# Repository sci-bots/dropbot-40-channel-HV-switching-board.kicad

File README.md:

# DropBot v3 40-channel high-voltage switching board

The high-voltage switching boards control the on/off state of electrodes in the [DropBot system][dropbot]. Each board controls 40-channels and multiple boards can be daisy-chained together.

For more information, please visit https://sci-bots.com

[][sci-bots]

This design is open-source hardware released under a [Creative Commons Attribution-ShareAlike licence][cc-by-sa].

[][cc-by-sa]

[dropbot]: https://github.com/sci-bots/dropbot-v3
[sci-bots]: https://sci-bots.com/
[cc-by-sa]: http://creativecommons.org/licenses/by-sa/3.0

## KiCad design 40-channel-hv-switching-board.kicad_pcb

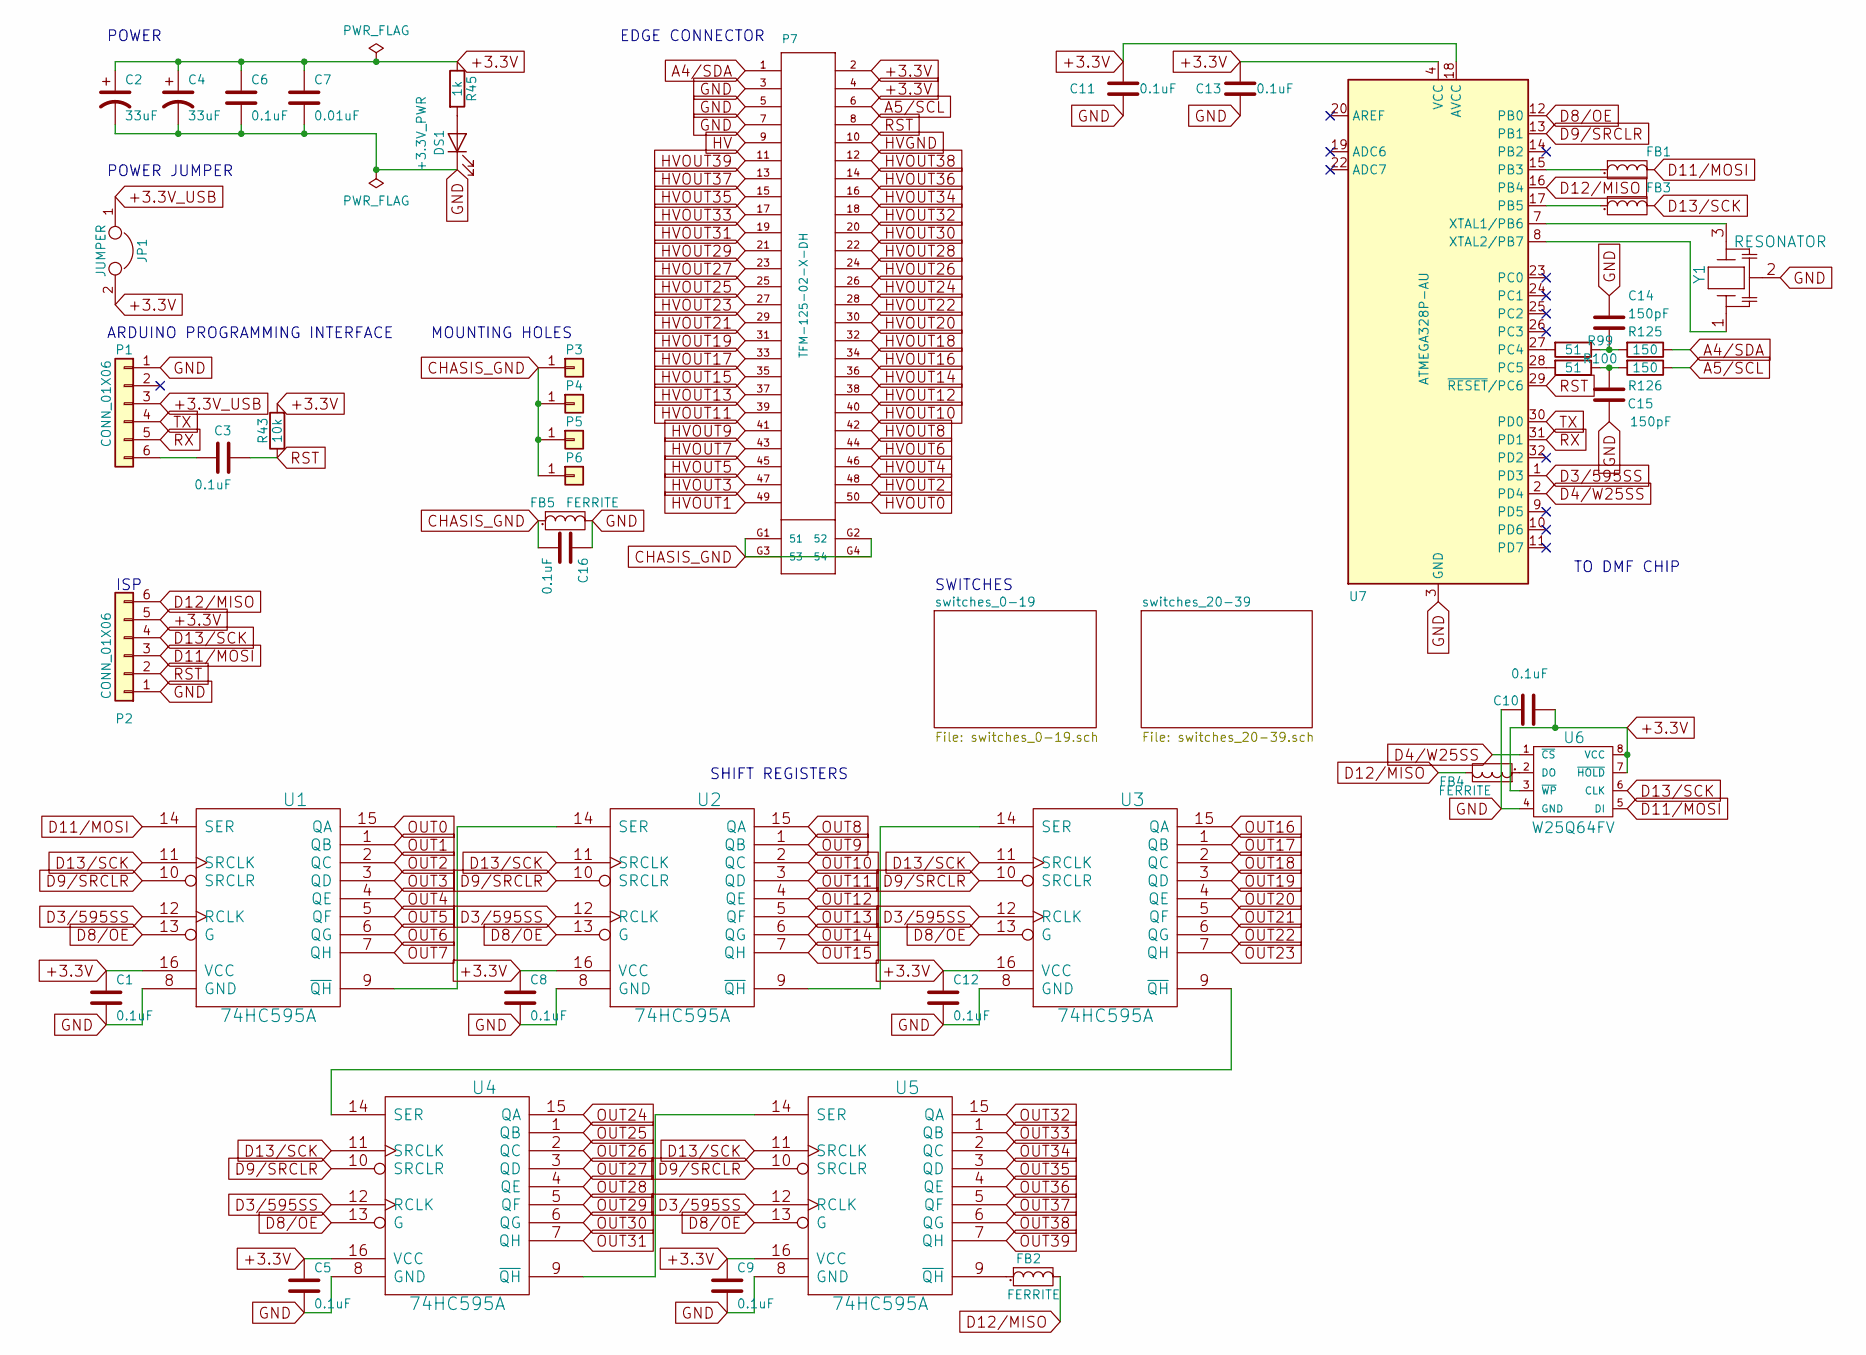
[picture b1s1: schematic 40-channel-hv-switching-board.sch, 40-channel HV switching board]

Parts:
C1, C3, C5, C6, C8, C9, C10, C11, C12, C13, C16: 0.1uF; C_0805; MPN CL21B104KBCNNNC
C2, C4: 33uF; SM2917; MPN T491D336K020AT
C7: 0.01uF; C_0805; MPN CL21B103KCANNNC
C14, C15: 150pF; C_0805; MPN CL21C151JBANNNC
DS1: +3.3V_PWR; LED_0805; MPN 150080BS75000
FB1, FB2, FB3, FB4, FB5: FERRITE; R_0805; MPN 742792040
JP1: JUMPER; R_0805; MPN DNP
P1: CONN_01X06; Pin_Header_Angled_1x06; MPN DNP
P2: CONN_01X06; Pin_Header_Straight_2x03; MPN DNP
P3, P4, P5, P6: CONN_01X01; 1pin; MPN DNP
P7: TFM-125-02-X-DH; MPN TFM-125-02-L-DH
R43: 10k; R_0805; MPN RC0805FR-0710KL
R45: 1k; R_0805; MPN RC0805FR-071KL
R99, R100: 51; R_0805; MPN RC0805FR-0751RL
R125, R126: 150; R_0805; MPN RC0805FR-07150RL
U1, U2, U3, U4, U5: 74HC595A; SO16E; MPN MM74HC595MX
U6: W25Q64FV; SOIC-8-N; MPN W25Q64FVSSIG TR
U7: ATMEGA328P-AU; TQFP-32_7x7mm_Pitch0.8mm; MPN ATMEGA328P-AU
Y1: RESONATOR; CSTCE_G15C; MPN CSTCE8M00G55-R0

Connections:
+3.3V: C1.1, C2.1, C4.1, C5.1, C6.1, C7.1, C8.1, C9.1, C10.1, C11.2, C12.1, C13.2, JP1.2, P2.5, P7.2, P7.4, R43.2, R45.1, U1.16 (VCC), U2.16 (VCC), U3.16 (VCC), U4.16 (VCC), U5.16 (VCC), U6.3 (~WP), U6.7 (~HOLD), U6.8 (VCC), U7.4 (VCC), U7.6 (VCC), U7.18 (AVCC); also elsewhere on the board
+3.3V_USB: JP1.1, P1.3
A4/SDA: P7.1, R125.1
A5/SCL: P7.6, R126.1
CHASIS_GND: C16.2, FB5.1, P3.1, P4.1, P5.1, P6.1, P7.G1 (51), P7.G2 (52), P7.G3 (53), P7.G4 (54)
D3/595SS: U1.12 (RCLK), U2.12 (RCLK), U3.12 (RCLK), U4.12 (RCLK), U5.12 (RCLK), U7.1 (PD3)
D4/W25SS: U6.1 (~CS), U7.2 (PD4)
D8/OE: U1.13 (G), U2.13 (G), U3.13 (G), U4.13 (G), U5.13 (G), U7.12 (PB0)
D9/SRCLR: U1.10 (SRCLR), U2.10 (SRCLR), U3.10 (SRCLR), U4.10 (SRCLR), U5.10 (SRCLR), U7.13 (PB1)
D11/MOSI: FB1.2, P2.3, U1.14 (SER), U6.5 (DI)
D12/MISO: FB2.2, FB4.2, P2.6, U7.16 (PB4)
D13/SCK: FB3.2, P2.4, U1.11 (SRCLK), U2.11 (SRCLK), U3.11 (SRCLK), U4.11 (SRCLK), U5.11 (SRCLK), U6.6 (CLK)
GND: C1.2, C2.2, C4.2, C5.2, C6.2, C7.2, C8.2, C9.2, C10.2, C11.1, C12.2, C13.1, C14.1, C15.1, C16.1, DS1.1 (K), FB5.2, P1.1, P2.1, P7.3, P7.5, P7.7, U1.8 (GND), U2.8 (GND), U3.8 (GND), U4.8 (GND), U5.8 (GND), U6.4 (GND), U7.3 (GND), U7.5 (GND), U7.21 (GND), Y1.2; also elsewhere on the board
HV: P7.9; also elsewhere on the board
HVGND: P7.10; also elsewhere on the board
HVOUT0: P7.50; also elsewhere on the board
HVOUT1: P7.49; also elsewhere on the board
HVOUT2: P7.48; also elsewhere on the board
HVOUT3: P7.47; also elsewhere on the board
HVOUT4: P7.46; also elsewhere on the board
HVOUT5: P7.45; also elsewhere on the board
HVOUT6: P7.44; also elsewhere on the board
HVOUT7: P7.43; also elsewhere on the board
HVOUT8: P7.42; also elsewhere on the board
HVOUT9: P7.41; also elsewhere on the board
HVOUT10: P7.40; also elsewhere on the board
HVOUT11: P7.39; also elsewhere on the board
HVOUT12: P7.38; also elsewhere on the board
HVOUT13: P7.37; also elsewhere on the board
HVOUT14: P7.36; also elsewhere on the board
HVOUT15: P7.35; also elsewhere on the board
HVOUT16: P7.34; also elsewhere on the board
HVOUT17: P7.33; also elsewhere on the board
HVOUT18: P7.32; also elsewhere on the board
HVOUT19: P7.31; also elsewhere on the board
HVOUT20: P7.30; also elsewhere on the board
HVOUT21: P7.29; also elsewhere on the board
HVOUT22: P7.28; also elsewhere on the board
HVOUT23: P7.27; also elsewhere on the board
HVOUT24: P7.26; also elsewhere on the board
HVOUT25: P7.25; also elsewhere on the board
HVOUT26: P7.24; also elsewhere on the board
HVOUT27: P7.23; also elsewhere on the board
HVOUT28: P7.22; also elsewhere on the board
HVOUT29: P7.21; also elsewhere on the board
HVOUT30: P7.20; also elsewhere on the board
HVOUT31: P7.19; also elsewhere on the board
HVOUT32: P7.18; also elsewhere on the board
HVOUT33: P7.17; also elsewhere on the board
HVOUT34: P7.16; also elsewhere on the board
HVOUT35: P7.15; also elsewhere on the board
HVOUT36: P7.14; also elsewhere on the board
HVOUT37: P7.13; also elsewhere on the board
HVOUT38: P7.12; also elsewhere on the board
HVOUT39: P7.11; also elsewhere on the board
unnamed: C3.1, P1.6
unnamed: C14.2, R99.1, R125.2
unnamed: C15.2, R100.1, R126.2
unnamed: DS1.2 (A), R45.2
unnamed: FB1.1, U7.15 (PB3)
unnamed: FB2.1, U5.9 (~QH)
unnamed: FB3.1, U7.17 (PB5)
unnamed: FB4.1, U6.2 (DO)
unnamed: R99.2, U7.27 (PC4)
unnamed: R100.2, U7.28 (PC5)
unnamed: U1.9 (~QH), U2.14 (SER)
unnamed: U2.9 (~QH), U3.14 (SER)
unnamed: U3.9 (~QH), U4.14 (SER)
unnamed: U4.9 (~QH), U5.14 (SER)
unnamed: U7.7 (XTAL1/PB6), Y1.3
unnamed: U7.8 (XTAL2/PB7), Y1.1
OUT0: U1.15 (QA); also elsewhere on the board
OUT1: U1.1 (QB); also elsewhere on the board
OUT2: U1.2 (QC); also elsewhere on the board
OUT3: U1.3 (QD); also elsewhere on the board
OUT4: U1.4 (QE); also elsewhere on the board
OUT5: U1.5 (QF); also elsewhere on the board
OUT6: U1.6 (QG); also elsewhere on the board
OUT7: U1.7 (QH); also elsewhere on the board
OUT8: U2.15 (QA); also elsewhere on the board
OUT9: U2.1 (QB); also elsewhere on the board
OUT10: U2.2 (QC); also elsewhere on the board
OUT11: U2.3 (QD); also elsewhere on the board
OUT12: U2.4 (QE); also elsewhere on the board
OUT13: U2.5 (QF); also elsewhere on the board
OUT14: U2.6 (QG); also elsewhere on the board
OUT15: U2.7 (QH); also elsewhere on the board
OUT16: U3.15 (QA); also elsewhere on the board
OUT17: U3.1 (QB); also elsewhere on the board
OUT18: U3.2 (QC); also elsewhere on the board
OUT19: U3.3 (QD); also elsewhere on the board
OUT20: U3.4 (QE); also elsewhere on the board
OUT21: U3.5 (QF); also elsewhere on the board
OUT22: U3.6 (QG); also elsewhere on the board
OUT23: U3.7 (QH); also elsewhere on the board
OUT24: U4.15 (QA); also elsewhere on the board
OUT25: U4.1 (QB); also elsewhere on the board
OUT26: U4.2 (QC); also elsewhere on the board
OUT27: U4.3 (QD); also elsewhere on the board
OUT28: U4.4 (QE); also elsewhere on the board
OUT29: U4.5 (QF); also elsewhere on the board
OUT30: U4.6 (QG); also elsewhere on the board
OUT31: U4.7 (QH); also elsewhere on the board
OUT32: U5.15 (QA); also elsewhere on the board
OUT33: U5.1 (QB); also elsewhere on the board
OUT34: U5.2 (QC); also elsewhere on the board
OUT35: U5.3 (QD); also elsewhere on the board
OUT36: U5.4 (QE); also elsewhere on the board
OUT37: U5.5 (QF); also elsewhere on the board
OUT38: U5.6 (QG); also elsewhere on the board
OUT39: U5.7 (QH); also elsewhere on the board
RST: C3.2, P2.2, P7.8, R43.1, U7.29 (~RESET~/PC6)
RX: P1.5, U7.31 (PD1)
TX: P1.4, U7.30 (PD0)

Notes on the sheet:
SHIFT REGISTERS
TO DMF CHIP
POWER
ARDUINO PROGRAMMING INTERFACE
ISP
POWER JUMPER
SWITCHES
EDGE CONNECTOR
MOUNTING HOLES

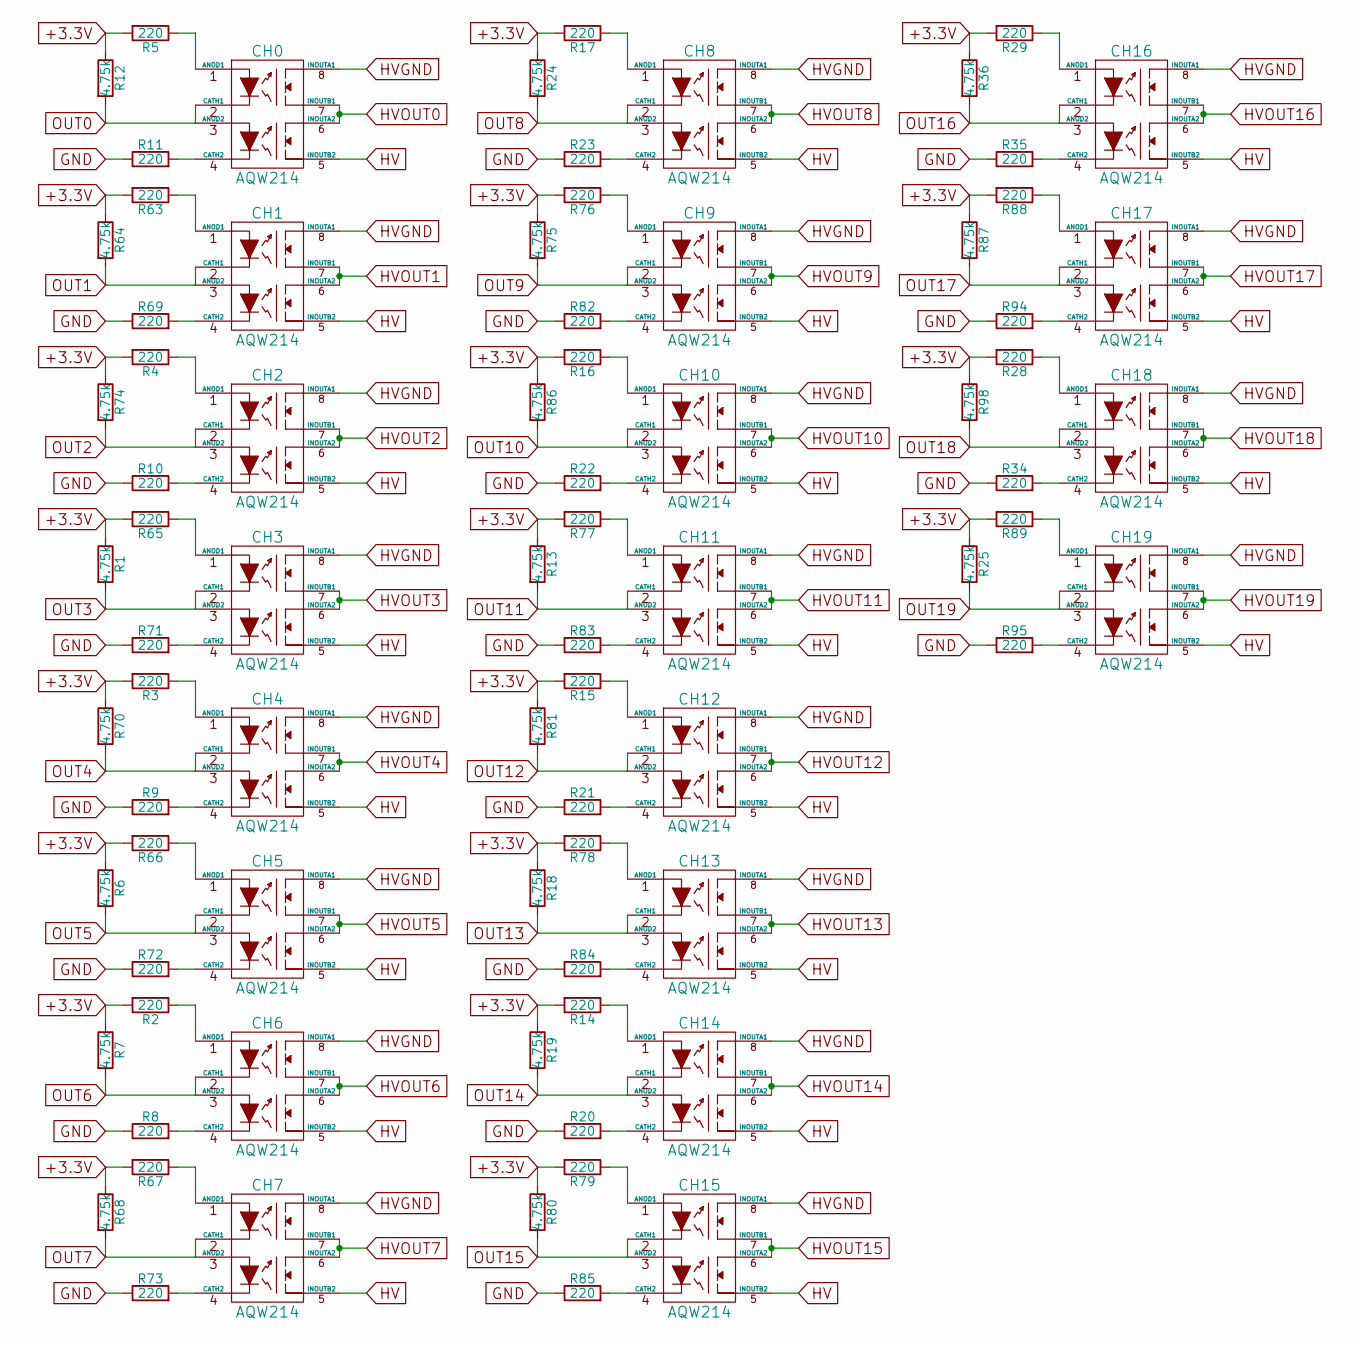
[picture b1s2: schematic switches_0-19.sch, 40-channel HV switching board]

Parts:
CH0, CH1, CH2, CH3, CH4, CH5, CH6, CH7, CH8, CH9, CH10, CH11, CH12, CH13, CH14, CH15, CH16, CH17, CH18, CH19: AQW214; DIP-8_SMD; Mfg_Part_No TLP227G-2(TP1,N,F)
R1, R6, R7, R12, R13, R18, R19, R25, R36, R64, R68, R70, R74, R75, R80, R81, R86, R87, R98: 4.75k; R_0805
R2, R3, R4, R5, R8, R9, R10, R11, R14, R15, R16, R17, R20, R21, R22, R23, R28, R29, R34, R35, R63, R65, R66, R69, R71, R72, R73, R76, R77, R78, R79, R82, R83, R84, R85, R88, R89, R94, R95: 220; R_0805
R24: 4.75k; R_0805; Mfg_Part_No RC0805FR-074K75L
R67: 220; R_0805; Mfg_Part_No RC0805FR-07220RL

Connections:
+3.3V: R1.1, R2.2, R3.2, R4.2, R5.2, R6.1, R7.1, R12.1, R13.1, R14.2, R15.2, R16.2, R17.2, R18.1, R19.1, R24.1, R25.1, R28.2, R29.2, R36.1, R63.2, R64.1, R65.2, R66.2, R67.2, R68.1, R70.1, R74.1, R75.1, R76.2, R77.2, R78.2, R79.2, R80.1, R81.1, R86.1, R87.1, R88.2, R89.2, R98.1; also elsewhere on the board
GND: R8.1, R9.1, R10.1, R11.1, R20.1, R21.1, R22.1, R23.1, R34.1, R35.1, R69.1, R71.1, R72.1, R73.1, R82.1, R83.1, R84.1, R85.1, R94.1, R95.1; also elsewhere on the board
HV: CH0.5 (INOUTB2), CH1.5 (INOUTB2), CH2.5 (INOUTB2), CH3.5 (INOUTB2), CH4.5 (INOUTB2), CH5.5 (INOUTB2), CH6.5 (INOUTB2), CH7.5 (INOUTB2), CH8.5 (INOUTB2), CH9.5 (INOUTB2), CH10.5 (INOUTB2), CH11.5 (INOUTB2), CH12.5 (INOUTB2), CH13.5 (INOUTB2), CH14.5 (INOUTB2), CH15.5 (INOUTB2), CH16.5 (INOUTB2), CH17.5 (INOUTB2), CH18.5 (INOUTB2), CH19.5 (INOUTB2); also elsewhere on the board
HVGND: CH0.8 (INOUTA1), CH1.8 (INOUTA1), CH2.8 (INOUTA1), CH3.8 (INOUTA1), CH4.8 (INOUTA1), CH5.8 (INOUTA1), CH6.8 (INOUTA1), CH7.8 (INOUTA1), CH8.8 (INOUTA1), CH9.8 (INOUTA1), CH10.8 (INOUTA1), CH11.8 (INOUTA1), CH12.8 (INOUTA1), CH13.8 (INOUTA1), CH14.8 (INOUTA1), CH15.8 (INOUTA1), CH16.8 (INOUTA1), CH17.8 (INOUTA1), CH18.8 (INOUTA1), CH19.8 (INOUTA1); also elsewhere on the board
HVOUT0: CH0.6 (INOUTA2), CH0.7 (INOUTB1); also elsewhere on the board
HVOUT1: CH1.6 (INOUTA2), CH1.7 (INOUTB1); also elsewhere on the board
HVOUT2: CH2.6 (INOUTA2), CH2.7 (INOUTB1); also elsewhere on the board
HVOUT3: CH3.6 (INOUTA2), CH3.7 (INOUTB1); also elsewhere on the board
HVOUT4: CH4.6 (INOUTA2), CH4.7 (INOUTB1); also elsewhere on the board
HVOUT5: CH5.6 (INOUTA2), CH5.7 (INOUTB1); also elsewhere on the board
HVOUT6: CH6.6 (INOUTA2), CH6.7 (INOUTB1); also elsewhere on the board
HVOUT7: CH7.6 (INOUTA2), CH7.7 (INOUTB1); also elsewhere on the board
HVOUT8: CH8.6 (INOUTA2), CH8.7 (INOUTB1); also elsewhere on the board
HVOUT9: CH9.6 (INOUTA2), CH9.7 (INOUTB1); also elsewhere on the board
HVOUT10: CH10.6 (INOUTA2), CH10.7 (INOUTB1); also elsewhere on the board
HVOUT11: CH11.6 (INOUTA2), CH11.7 (INOUTB1); also elsewhere on the board
HVOUT12: CH12.6 (INOUTA2), CH12.7 (INOUTB1); also elsewhere on the board
HVOUT13: CH13.6 (INOUTA2), CH13.7 (INOUTB1); also elsewhere on the board
HVOUT14: CH14.6 (INOUTA2), CH14.7 (INOUTB1); also elsewhere on the board
HVOUT15: CH15.6 (INOUTA2), CH15.7 (INOUTB1); also elsewhere on the board
HVOUT16: CH16.6 (INOUTA2), CH16.7 (INOUTB1); also elsewhere on the board
HVOUT17: CH17.6 (INOUTA2), CH17.7 (INOUTB1); also elsewhere on the board
HVOUT18: CH18.6 (INOUTA2), CH18.7 (INOUTB1); also elsewhere on the board
HVOUT19: CH19.6 (INOUTA2), CH19.7 (INOUTB1); also elsewhere on the board
unnamed: CH0.1 (ANOD1), R5.1
unnamed: CH0.4 (CATH2), R11.2
unnamed: CH1.1 (ANOD1), R63.1
unnamed: CH1.4 (CATH2), R69.2
unnamed: CH2.1 (ANOD1), R4.1
unnamed: CH2.4 (CATH2), R10.2
unnamed: CH3.1 (ANOD1), R65.1
unnamed: CH3.4 (CATH2), R71.2
unnamed: CH4.1 (ANOD1), R3.1
unnamed: CH4.4 (CATH2), R9.2
unnamed: CH5.1 (ANOD1), R66.1
unnamed: CH5.4 (CATH2), R72.2
unnamed: CH6.1 (ANOD1), R2.1
unnamed: CH6.4 (CATH2), R8.2
unnamed: CH7.1 (ANOD1), R67.1
unnamed: CH7.4 (CATH2), R73.2
unnamed: CH8.1 (ANOD1), R17.1
unnamed: CH8.4 (CATH2), R23.2
unnamed: CH9.1 (ANOD1), R76.1
unnamed: CH9.4 (CATH2), R82.2
unnamed: CH10.1 (ANOD1), R16.1
unnamed: CH10.4 (CATH2), R22.2
unnamed: CH11.1 (ANOD1), R77.1
unnamed: CH11.4 (CATH2), R83.2
unnamed: CH12.1 (ANOD1), R15.1
unnamed: CH12.4 (CATH2), R21.2
unnamed: CH13.1 (ANOD1), R78.1
unnamed: CH13.4 (CATH2), R84.2
unnamed: CH14.1 (ANOD1), R14.1
unnamed: CH14.4 (CATH2), R20.2
unnamed: CH15.1 (ANOD1), R79.1
unnamed: CH15.4 (CATH2), R85.2
unnamed: CH16.1 (ANOD1), R29.1
unnamed: CH16.4 (CATH2), R35.2
unnamed: CH17.1 (ANOD1), R88.1
unnamed: CH17.4 (CATH2), R94.2
unnamed: CH18.1 (ANOD1), R28.1
unnamed: CH18.4 (CATH2), R34.2
unnamed: CH19.1 (ANOD1), R89.1
unnamed: CH19.4 (CATH2), R95.2
OUT0: CH0.2 (CATH1), CH0.3 (ANOD2), R12.2; also elsewhere on the board
OUT1: CH1.2 (CATH1), CH1.3 (ANOD2), R64.2; also elsewhere on the board
OUT2: CH2.2 (CATH1), CH2.3 (ANOD2), R74.2; also elsewhere on the board
OUT3: CH3.2 (CATH1), CH3.3 (ANOD2), R1.2; also elsewhere on the board
OUT4: CH4.2 (CATH1), CH4.3 (ANOD2), R70.2; also elsewhere on the board
OUT5: CH5.2 (CATH1), CH5.3 (ANOD2), R6.2; also elsewhere on the board
OUT6: CH6.2 (CATH1), CH6.3 (ANOD2), R7.2; also elsewhere on the board
OUT7: CH7.2 (CATH1), CH7.3 (ANOD2), R68.2; also elsewhere on the board
OUT8: CH8.2 (CATH1), CH8.3 (ANOD2), R24.2; also elsewhere on the board
OUT9: CH9.2 (CATH1), CH9.3 (ANOD2), R75.2; also elsewhere on the board
OUT10: CH10.2 (CATH1), CH10.3 (ANOD2), R86.2; also elsewhere on the board
OUT11: CH11.2 (CATH1), CH11.3 (ANOD2), R13.2; also elsewhere on the board
OUT12: CH12.2 (CATH1), CH12.3 (ANOD2), R81.2; also elsewhere on the board
OUT13: CH13.2 (CATH1), CH13.3 (ANOD2), R18.2; also elsewhere on the board
OUT14: CH14.2 (CATH1), CH14.3 (ANOD2), R19.2; also elsewhere on the board
OUT15: CH15.2 (CATH1), CH15.3 (ANOD2), R80.2; also elsewhere on the board
OUT16: CH16.2 (CATH1), CH16.3 (ANOD2), R36.2; also elsewhere on the board
OUT17: CH17.2 (CATH1), CH17.3 (ANOD2), R87.2; also elsewhere on the board
OUT18: CH18.2 (CATH1), CH18.3 (ANOD2), R98.2; also elsewhere on the board
OUT19: CH19.2 (CATH1), CH19.3 (ANOD2), R25.2; also elsewhere on the board

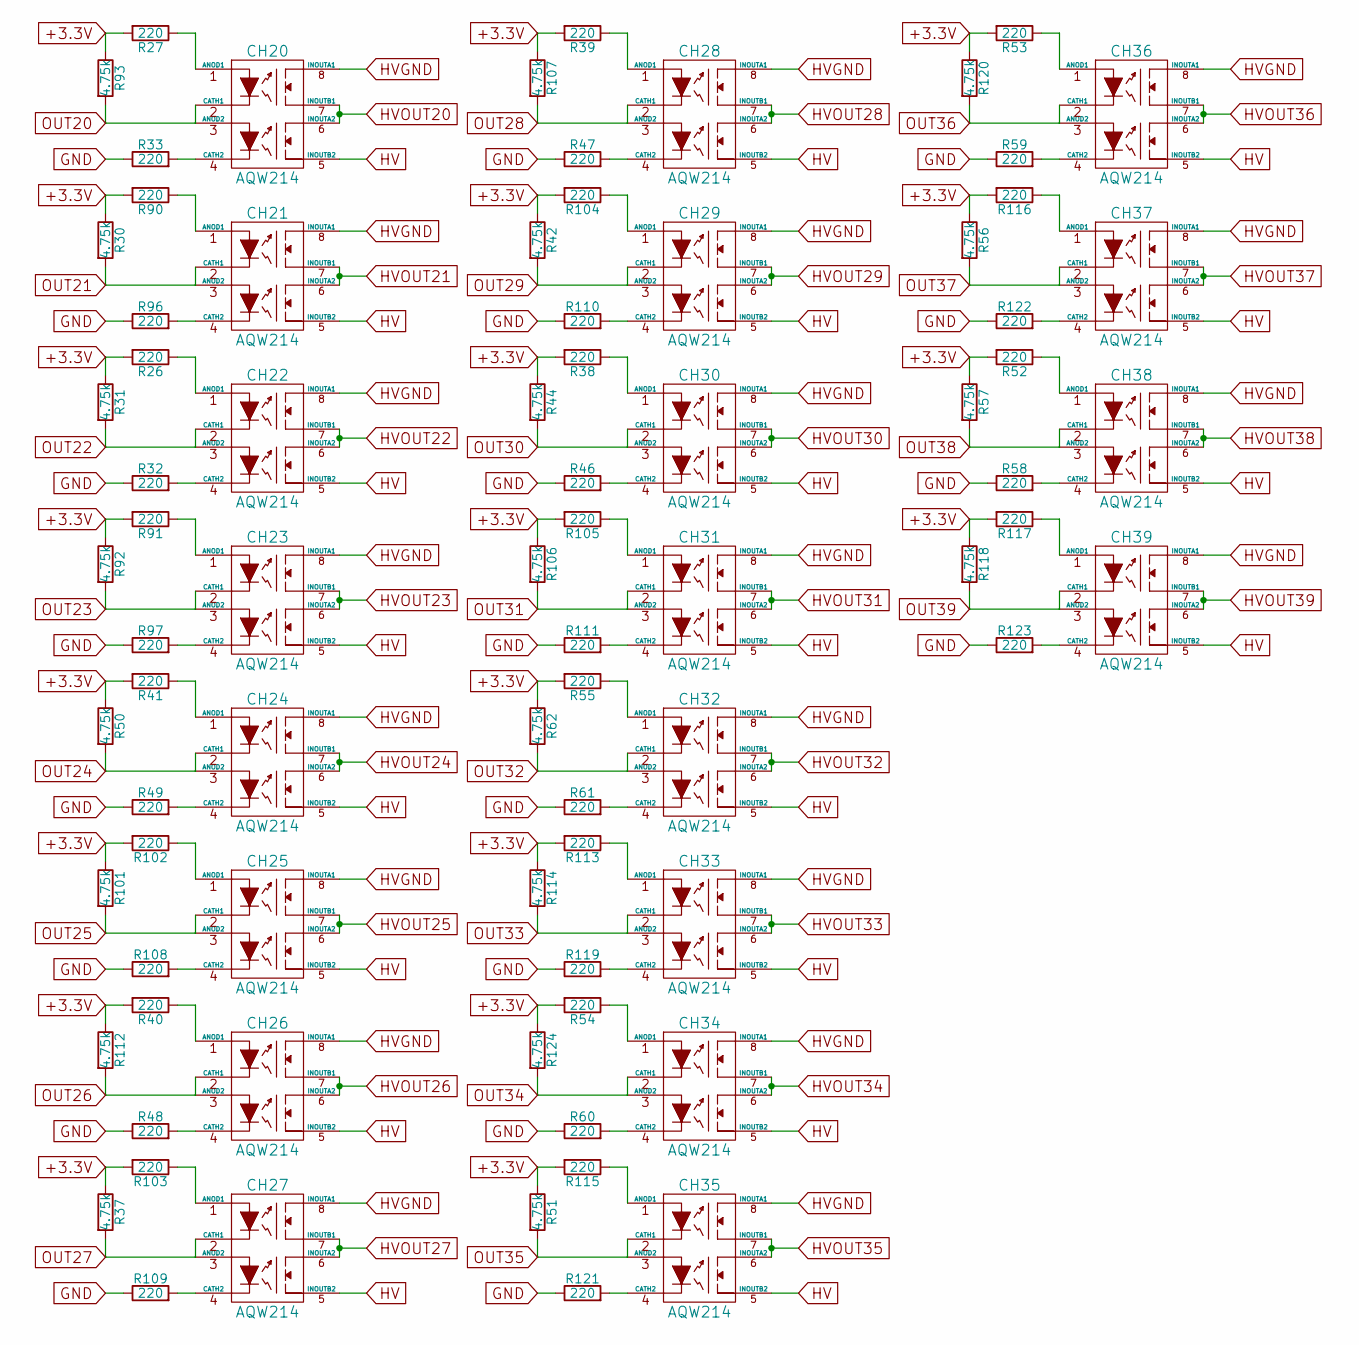
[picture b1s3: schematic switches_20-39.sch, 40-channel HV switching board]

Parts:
CH20, CH21, CH22, CH23, CH24, CH25, CH26, CH27, CH28, CH29, CH30, CH31, CH32, CH33, CH34, CH35, CH36, CH37, CH38, CH39: AQW214; DIP-8_SMD; Mfg_Part_No TLP227G-2(TP1,N,F)
R26, R27, R32, R33, R38, R39, R40, R41, R46, R47, R48, R49, R52, R53, R54, R55, R58, R59, R60, R61, R90, R91, R96, R97, R102, R103, R104, R105, R108, R109, R110, R111, R113, R115, R116, R117, R119, R121, R122, R123: 220; R_0805
R30, R31, R37, R42, R44, R50, R51, R56, R57, R62, R92, R93, R101, R106, R107, R112, R114, R118, R120, R124: 4.75k; R_0805

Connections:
+3.3V: R26.2, R27.2, R30.1, R31.1, R37.1, R38.2, R39.2, R40.2, R41.2, R42.1, R44.1, R50.1, R51.1, R52.2, R53.2, R54.2, R55.2, R56.1, R57.1, R62.1, R90.2, R91.2, R92.1, R93.1, R101.1, R102.2, R103.2, R104.2, R105.2, R106.1, R107.1, R112.1, R113.2, R114.1, R115.2, R116.2, R117.2, R118.1, R120.1, R124.1; also elsewhere on the board
GND: R32.1, R33.1, R46.1, R47.1, R48.1, R49.1, R58.1, R59.1, R60.1, R61.1, R96.1, R97.1, R108.1, R109.1, R110.1, R111.1, R119.1, R121.1, R122.1, R123.1; also elsewhere on the board
HV: CH20.5 (INOUTB2), CH21.5 (INOUTB2), CH22.5 (INOUTB2), CH23.5 (INOUTB2), CH24.5 (INOUTB2), CH25.5 (INOUTB2), CH26.5 (INOUTB2), CH27.5 (INOUTB2), CH28.5 (INOUTB2), CH29.5 (INOUTB2), CH30.5 (INOUTB2), CH31.5 (INOUTB2), CH32.5 (INOUTB2), CH33.5 (INOUTB2), CH34.5 (INOUTB2), CH35.5 (INOUTB2), CH36.5 (INOUTB2), CH37.5 (INOUTB2), CH38.5 (INOUTB2), CH39.5 (INOUTB2); also elsewhere on the board
HVGND: CH20.8 (INOUTA1), CH21.8 (INOUTA1), CH22.8 (INOUTA1), CH23.8 (INOUTA1), CH24.8 (INOUTA1), CH25.8 (INOUTA1), CH26.8 (INOUTA1), CH27.8 (INOUTA1), CH28.8 (INOUTA1), CH29.8 (INOUTA1), CH30.8 (INOUTA1), CH31.8 (INOUTA1), CH32.8 (INOUTA1), CH33.8 (INOUTA1), CH34.8 (INOUTA1), CH35.8 (INOUTA1), CH36.8 (INOUTA1), CH37.8 (INOUTA1), CH38.8 (INOUTA1), CH39.8 (INOUTA1); also elsewhere on the board
HVOUT20: CH20.6 (INOUTA2), CH20.7 (INOUTB1); also elsewhere on the board
HVOUT21: CH21.6 (INOUTA2), CH21.7 (INOUTB1); also elsewhere on the board
HVOUT22: CH22.6 (INOUTA2), CH22.7 (INOUTB1); also elsewhere on the board
HVOUT23: CH23.6 (INOUTA2), CH23.7 (INOUTB1); also elsewhere on the board
HVOUT24: CH24.6 (INOUTA2), CH24.7 (INOUTB1); also elsewhere on the board
HVOUT25: CH25.6 (INOUTA2), CH25.7 (INOUTB1); also elsewhere on the board
HVOUT26: CH26.6 (INOUTA2), CH26.7 (INOUTB1); also elsewhere on the board
HVOUT27: CH27.6 (INOUTA2), CH27.7 (INOUTB1); also elsewhere on the board
HVOUT28: CH28.6 (INOUTA2), CH28.7 (INOUTB1); also elsewhere on the board
HVOUT29: CH29.6 (INOUTA2), CH29.7 (INOUTB1); also elsewhere on the board
HVOUT30: CH30.6 (INOUTA2), CH30.7 (INOUTB1); also elsewhere on the board
HVOUT31: CH31.6 (INOUTA2), CH31.7 (INOUTB1); also elsewhere on the board
HVOUT32: CH32.6 (INOUTA2), CH32.7 (INOUTB1); also elsewhere on the board
HVOUT33: CH33.6 (INOUTA2), CH33.7 (INOUTB1); also elsewhere on the board
HVOUT34: CH34.6 (INOUTA2), CH34.7 (INOUTB1); also elsewhere on the board
HVOUT35: CH35.6 (INOUTA2), CH35.7 (INOUTB1); also elsewhere on the board
HVOUT36: CH36.6 (INOUTA2), CH36.7 (INOUTB1); also elsewhere on the board
HVOUT37: CH37.6 (INOUTA2), CH37.7 (INOUTB1); also elsewhere on the board
HVOUT38: CH38.6 (INOUTA2), CH38.7 (INOUTB1); also elsewhere on the board
HVOUT39: CH39.6 (INOUTA2), CH39.7 (INOUTB1); also elsewhere on the board
unnamed: CH20.1 (ANOD1), R27.1
unnamed: CH20.4 (CATH2), R33.2
unnamed: CH21.1 (ANOD1), R90.1
unnamed: CH21.4 (CATH2), R96.2
unnamed: CH22.1 (ANOD1), R26.1
unnamed: CH22.4 (CATH2), R32.2
unnamed: CH23.1 (ANOD1), R91.1
unnamed: CH23.4 (CATH2), R97.2
unnamed: CH24.1 (ANOD1), R41.1
unnamed: CH24.4 (CATH2), R49.2
unnamed: CH25.1 (ANOD1), R102.1
unnamed: CH25.4 (CATH2), R108.2
unnamed: CH26.1 (ANOD1), R40.1
unnamed: CH26.4 (CATH2), R48.2
unnamed: CH27.1 (ANOD1), R103.1
unnamed: CH27.4 (CATH2), R109.2
unnamed: CH28.1 (ANOD1), R39.1
unnamed: CH28.4 (CATH2), R47.2
unnamed: CH29.1 (ANOD1), R104.1
unnamed: CH29.4 (CATH2), R110.2
unnamed: CH30.1 (ANOD1), R38.1
unnamed: CH30.4 (CATH2), R46.2
unnamed: CH31.1 (ANOD1), R105.1
unnamed: CH31.4 (CATH2), R111.2
unnamed: CH32.1 (ANOD1), R55.1
unnamed: CH32.4 (CATH2), R61.2
unnamed: CH33.1 (ANOD1), R113.1
unnamed: CH33.4 (CATH2), R119.2
unnamed: CH34.1 (ANOD1), R54.1
unnamed: CH34.4 (CATH2), R60.2
unnamed: CH35.1 (ANOD1), R115.1
unnamed: CH35.4 (CATH2), R121.2
unnamed: CH36.1 (ANOD1), R53.1
unnamed: CH36.4 (CATH2), R59.2
unnamed: CH37.1 (ANOD1), R116.1
unnamed: CH37.4 (CATH2), R122.2
unnamed: CH38.1 (ANOD1), R52.1
unnamed: CH38.4 (CATH2), R58.2
unnamed: CH39.1 (ANOD1), R117.1
unnamed: CH39.4 (CATH2), R123.2
OUT20: CH20.2 (CATH1), CH20.3 (ANOD2), R93.2; also elsewhere on the board
OUT21: CH21.2 (CATH1), CH21.3 (ANOD2), R30.2; also elsewhere on the board
OUT22: CH22.2 (CATH1), CH22.3 (ANOD2), R31.2; also elsewhere on the board
OUT23: CH23.2 (CATH1), CH23.3 (ANOD2), R92.2; also elsewhere on the board
OUT24: CH24.2 (CATH1), CH24.3 (ANOD2), R50.2; also elsewhere on the board
OUT25: CH25.2 (CATH1), CH25.3 (ANOD2), R101.2; also elsewhere on the board
OUT26: CH26.2 (CATH1), CH26.3 (ANOD2), R112.2; also elsewhere on the board
OUT27: CH27.2 (CATH1), CH27.3 (ANOD2), R37.2; also elsewhere on the board
OUT28: CH28.2 (CATH1), CH28.3 (ANOD2), R107.2; also elsewhere on the board
OUT29: CH29.2 (CATH1), CH29.3 (ANOD2), R42.2; also elsewhere on the board
OUT30: CH30.2 (CATH1), CH30.3 (ANOD2), R44.2; also elsewhere on the board
OUT31: CH31.2 (CATH1), CH31.3 (ANOD2), R106.2; also elsewhere on the board
OUT32: CH32.2 (CATH1), CH32.3 (ANOD2), R62.2; also elsewhere on the board
OUT33: CH33.2 (CATH1), CH33.3 (ANOD2), R114.2; also elsewhere on the board
OUT34: CH34.2 (CATH1), CH34.3 (ANOD2), R124.2; also elsewhere on the board
OUT35: CH35.2 (CATH1), CH35.3 (ANOD2), R51.2; also elsewhere on the board
OUT36: CH36.2 (CATH1), CH36.3 (ANOD2), R120.2; also elsewhere on the board
OUT37: CH37.2 (CATH1), CH37.3 (ANOD2), R56.2; also elsewhere on the board
OUT38: CH38.2 (CATH1), CH38.3 (ANOD2), R57.2; also elsewhere on the board
OUT39: CH39.2 (CATH1), CH39.3 (ANOD2), R118.2; also elsewhere on the board

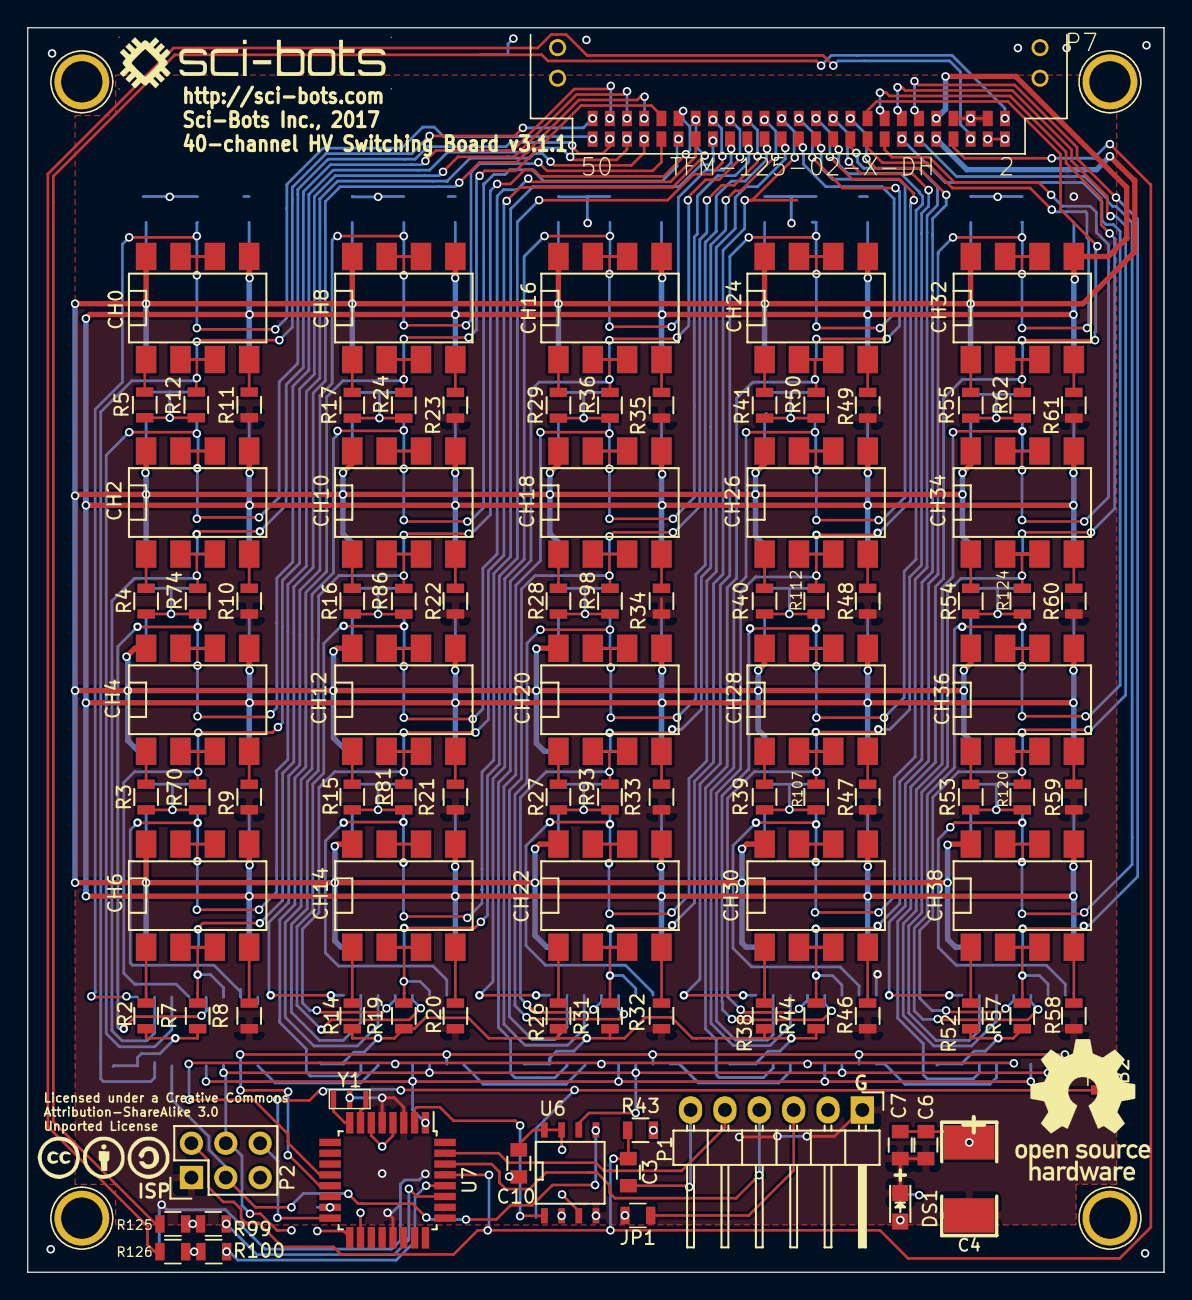
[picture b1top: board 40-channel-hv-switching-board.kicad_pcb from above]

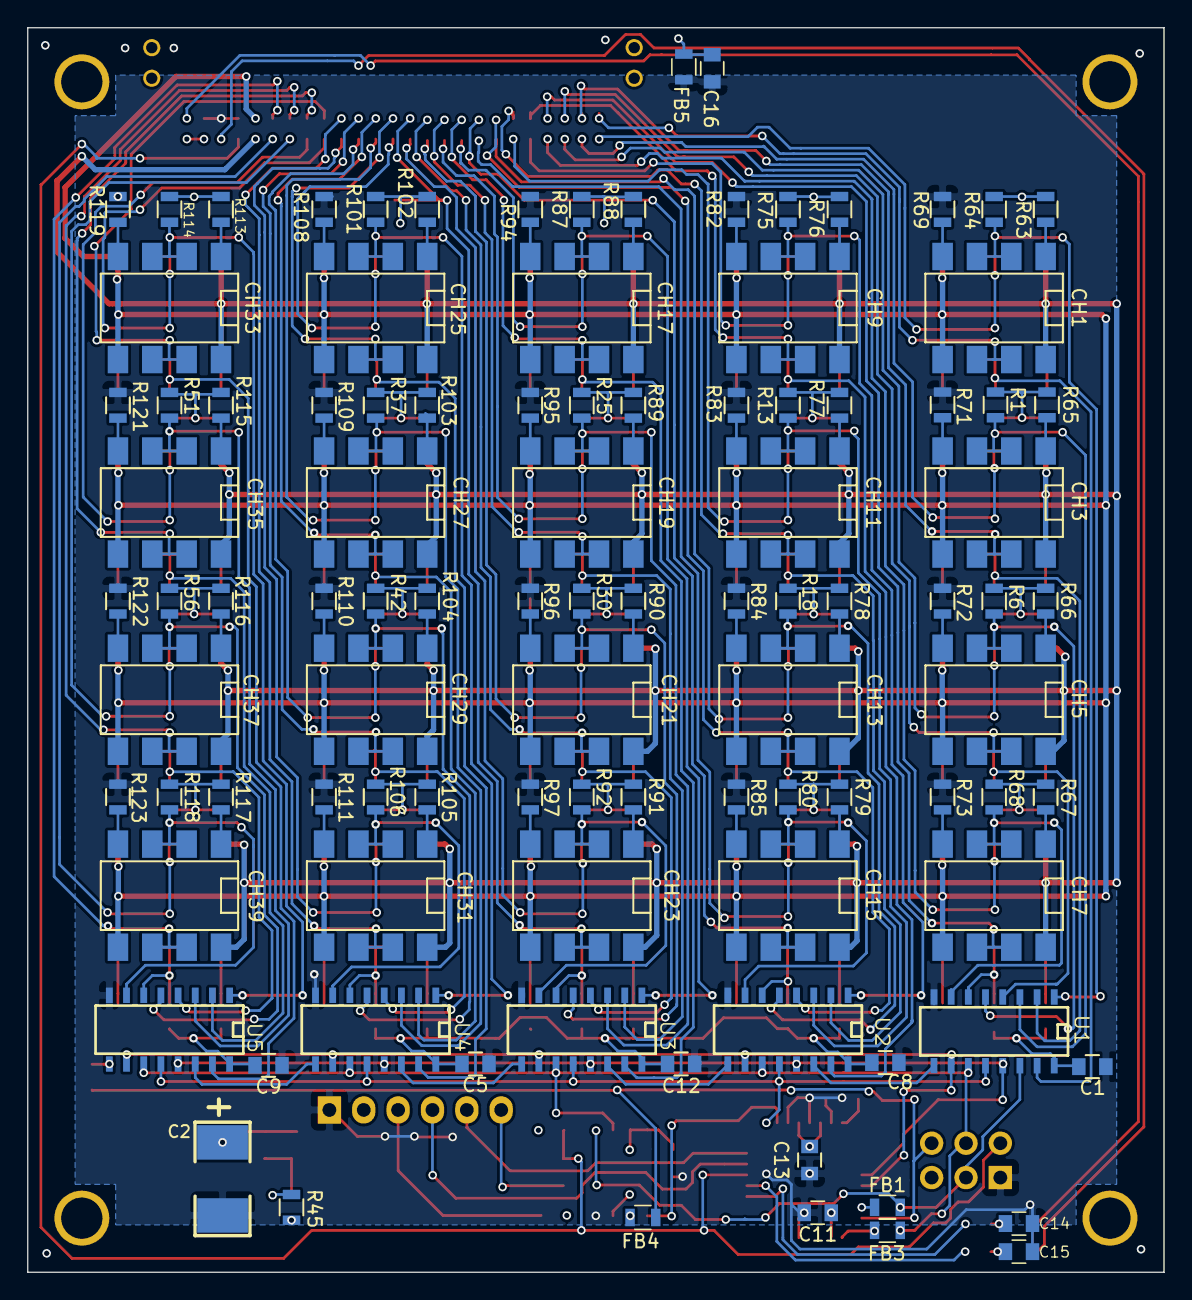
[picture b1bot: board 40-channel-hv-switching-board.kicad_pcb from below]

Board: 4 copper layers, 84.0 x 92.0 mm, 204 parts (101 on the bottom side), 194 nets.

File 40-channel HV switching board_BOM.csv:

Reference,Value,Footprint,Count,Datasheet,Mfg_Part_No
DS1,+3.3V_PWR,LEDs:LED_0805,1,,150080BS75000
R45,1k,Resistors_SMD:R_0805,1,,RC0805FR-071KL
C7,0.01uF,Capacitors_SMD:C_0805,1,,CL21B103KCANNNC
"C4, C2",33uF,Sci-Bots:SM2917,2,,T491D336K020AT
"C6, C3, C13, C1, C8, C12, C5, C9, C10, C11, C16",0.1uF,Capacitors_SMD:C_0805,11,,CL21B104KBCNNNC
R43,10k,Resistors_SMD:R_0805,1,,RC0805FR-0710KL
"U1, U2, U3, U4, U5",74HC595A,Sci-Bots:SO16E,5,,MM74HC595MX
P2,CONN_01X06,Pin_Headers:Pin_Header_Straight_2x03,1,,
P1,CONN_01X06,Pin_Headers:Pin_Header_Angled_1x06,1,,
Y1,RESONATOR,Sci-Bots:CSTCE_G15C,1,http://www.murata.com/~/media/webrenewal/support/library/cat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,CSTCE8M00G55-R0
JP1,JUMPER,Resistors_SMD:R_0805,1,,
U6,W25Q64FV,SMD_Packages:SOIC-8-N,1,,W25Q64FVSSIG TR
P7,TFM-125-02-X-DH,Sci-Bots:TFM-125-02-X-DH,1,,TFM-125-02-L-DH
"P3, P4, P5, P6",CONN_01X01,Connect:1pin,4,,
"FB1, FB2, FB3, FB4, FB5",FERRITE,Resistors_SMD:R_0805,5,,742792040
"C15, C14",150pF,Capacitors_SMD:C_0805,2,,CL21C151JBANNNC
"R99, R100",51,Resistors_SMD:R_0805,2,,RC0805FR-0751RL
"R125, R126",150,Resistors_SMD:R_0805,2,,RC0805FR-07150RL
U7,ATMEGA328P-AU,Housings_QFP:TQFP-32_7x7mm_Pitch0.8mm,1,,ATMEGA328P-AU
"R24, R12, R64, R74, R1, R70, R6, R7, R68, R75, R86, R13, R81, R18, R19, R80, R36, R87, R98, R25, R107, R93, R30, R31, R92, R50, R101, R112, R37, R42, R44, R106, R62, R114, R124, R51, R120, R56, R57, R118",4.75k,Resistors_SMD:R_0805,40,,RC0805FR-074K75L
"R67, R73, R8, R2, R65, R71, R72, R66, R3, R9, R10, R4, R63, R69, R11, R5, R79, R85, R20, R14, R15, R21, R84, R78, R16, R22, R83, R77, R76, R23, R17, R28, R34, R95, R89, R88, R94, R35, R29, R82, R103, R109, R48, R40, R41, R49, R108, R102, R26, R32, R97, R91, R90, R96, R33, R27, R115, R121, R60, R54, R55, R61, R119, R113, R38, R46, R111, R105, R104, R110, R47, R39, R52, R58, R123, R117, R116, R122, R59, R53",220,Resistors_SMD:R_0805,80,,RC0805FR-07220RL
"CH7, CH6, CH4, CH5, CH2, CH3, CH0, CH1, CH15, CH14, CH12, CH13, CH10, CH11, CH8, CH9, CH18, CH19, CH16, CH17, CH27, CH26, CH24, CH25, CH22, CH23, CH20, CH21, CH35, CH34, CH32, CH33, CH30, CH31, CH28, CH29, CH38, CH39, CH36, CH37",SSR-DPST,SMD_Packages:DIP-8_SMD,40,,"TLP227G-2(TP1,N,F)"

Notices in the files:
40-channel-hv-switching-board.kicad_pcb:
Licensed under a Creative Commons
Attribution-ShareAlike 3.0
